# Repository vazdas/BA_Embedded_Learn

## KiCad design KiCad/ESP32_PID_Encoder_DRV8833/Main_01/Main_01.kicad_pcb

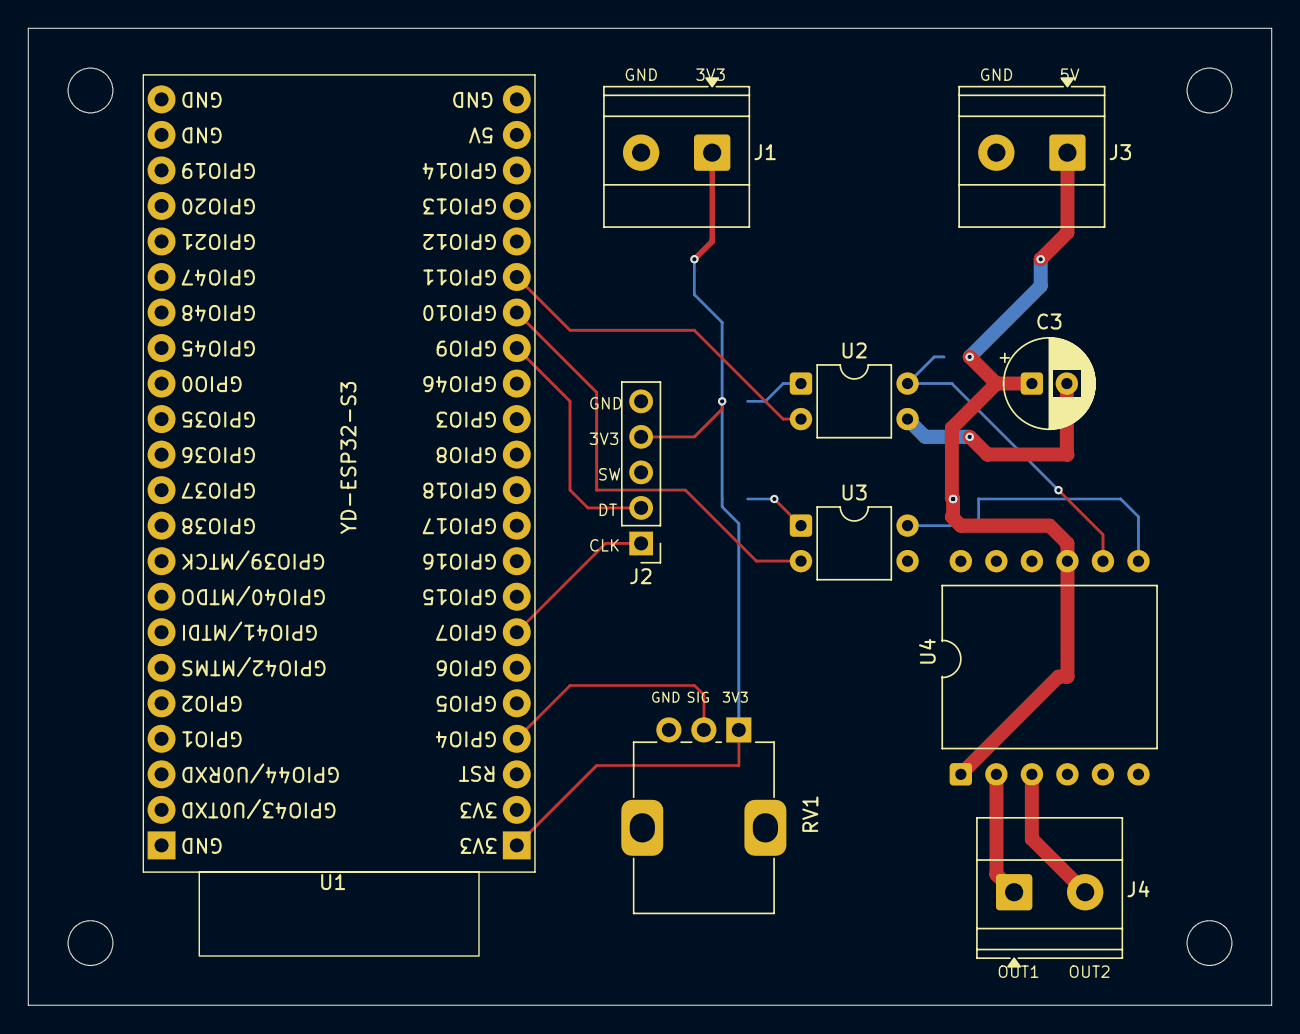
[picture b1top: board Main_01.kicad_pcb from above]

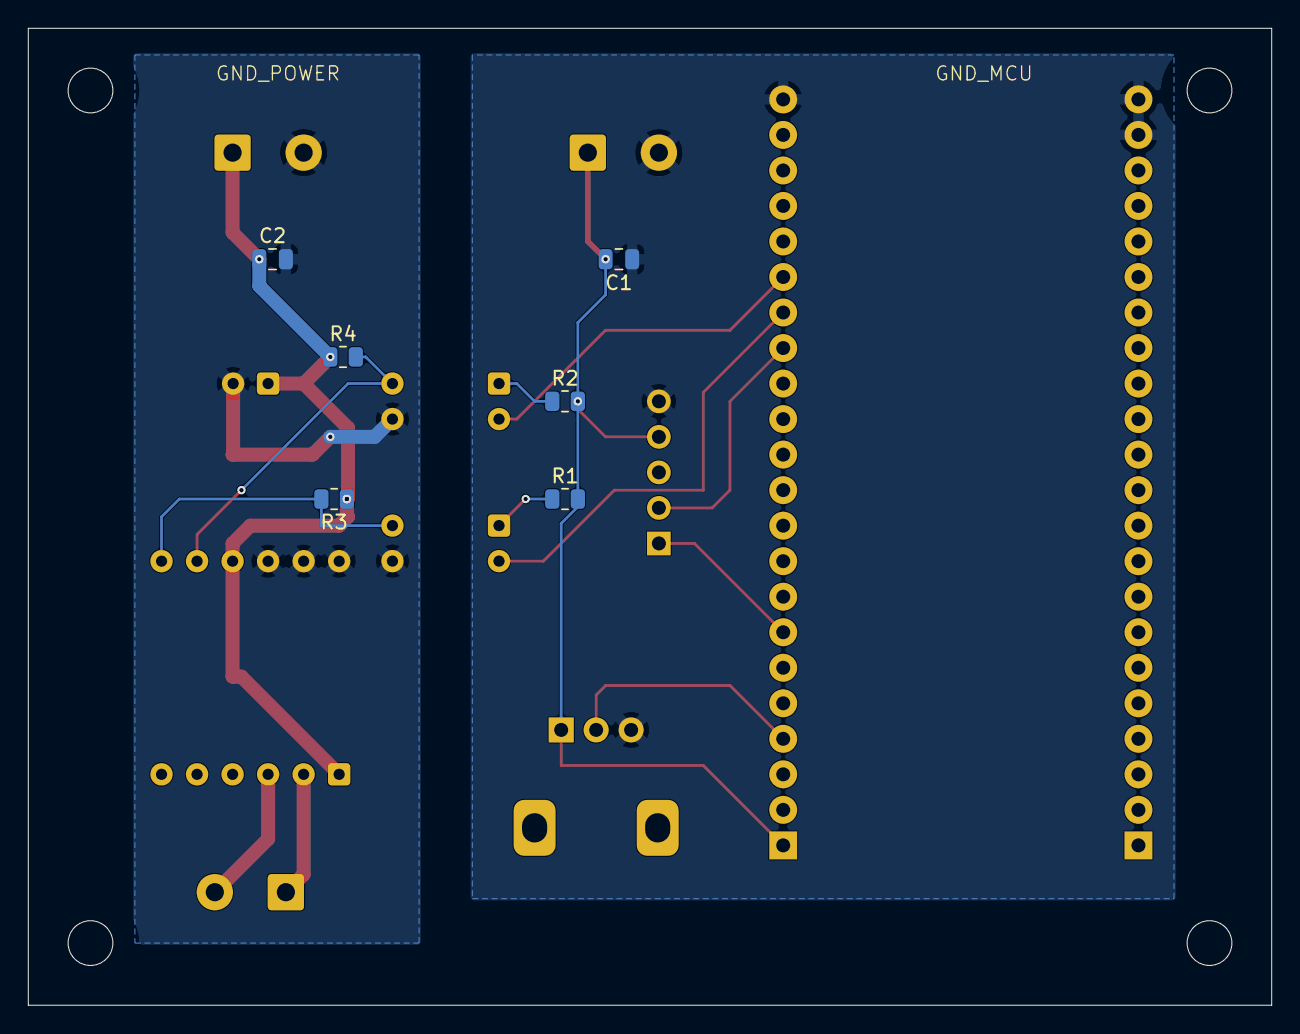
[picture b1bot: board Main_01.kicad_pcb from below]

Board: 2 copper layers, 88.9 x 69.8 mm, 16 parts (6 on the bottom side), 15 nets.

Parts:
C1, C2: 0.1u; C_0805_2012Metric
C3: 100u; CP_Radial_D6.3mm_P2.50mm
J1: 3V3; TerminalBlock_Phoenix_MKDS-1,5-2-5.08_1x02_P5.08mm_Horizont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
J2: Encoder KY-040; PinHeader_1x05_P2.54mm_Vertical
J3: PWR_5V; TerminalBlock_Phoenix_MKDS-1,5-2-5.08_1x02_P5.08mm_Horizont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
J4: Motor_Out; TerminalBlock_Phoenix_MKDS-1,5-2-5.08_1x02_P5.08mm_Horizont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
R1, R2: 150; R_0805_2012Metric
R3, R4: 10k; R_0805_2012Metric
RV1: R_Potentiometer; Potentiometer_Alps_RK09K_Single_Vertical
U1: YD-ESP32-S3
U2, U3: PC817; DIP-4_W7.62mm
U4: DRV8833; DRV8833_W15.24mm

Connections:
+3.3V: C1.2, J1.1 (3V3), J2.4, R1.2, R2.2, RV1.1, U1.1 (3V3)
+5V: C2.1, C3.1, J3.1 (5V), R3.1, R4.1, U4.1 (EEP), U4.9 (VCC)
GND: C1.1, J1.2 (GND), J2.5, RV1.3, U1.22 (GND), U1.23 (GND), U1.24 (GND)
GND_POWER: C2.2, C3.2, J3.2 (GND), U2.3, U3.3, U4.10 (GND), U4.11 (IN3), U4.12 (IN4)
unnamed: J2.1, U1.7 (GPIO7)
unnamed: J2.2, U1.15 (GPIO9)
unnamed: J4.1 (OUT1), U4.2 (OUT1)
unnamed: J4.2 (OUT2), U4.3 (OUT2)
unnamed: R1.1, U3.1
unnamed: R2.1, U2.1
unnamed: RV1.2, U1.4 (GPIO4)
unnamed: U1.16 (GPIO10), U3.2
unnamed: U1.17 (GPIO11), U2.2
unnamed: R3.2, U3.4, U4.7 (IN1)
unnamed: R4.2, U2.4, U4.8 (IN2)
